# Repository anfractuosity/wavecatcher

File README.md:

# wavecatcher

https://www.anfractuosity.com/projects/wavecatcher/ - please see this website for more detail on the project.

The project will be used for acoustic cryptanalysis - "Acoustic cryptanalysis is a type of side channel attack that exploits sounds emitted by computers or other devices".

A number of aspects of computers emit ultrasound including SMPSs to inductors and capacitors present on the computer's motherboard itself.

You will likely require Kicad 5 to use the schematic/pcb layouts.

## Software

The software is now capable of extracting audio from the PDM microphone enabling playing of the audio with SoX.

I now need to swap the simple summing PDM to PCM converter, to enable better fidelity audio.

## Hardware

The PCB was manufactured and assembled using Macrofab.  I plan to eventually revise the PCB at some point
making use of line length matching of USB tracks and more curved PCB tracks.

I conducted a little benchmark of the STM32F3 chip's USB performance and get roughly 6Mbps received from it on my computer. The bandwidth
may vary a fair bit, in the order of megabits depending on your USB controller!

## Creative Commons Licence

Attribution-NonCommercial-ShareAlike 4.0 International (CC BY-NC-SA 4.0)

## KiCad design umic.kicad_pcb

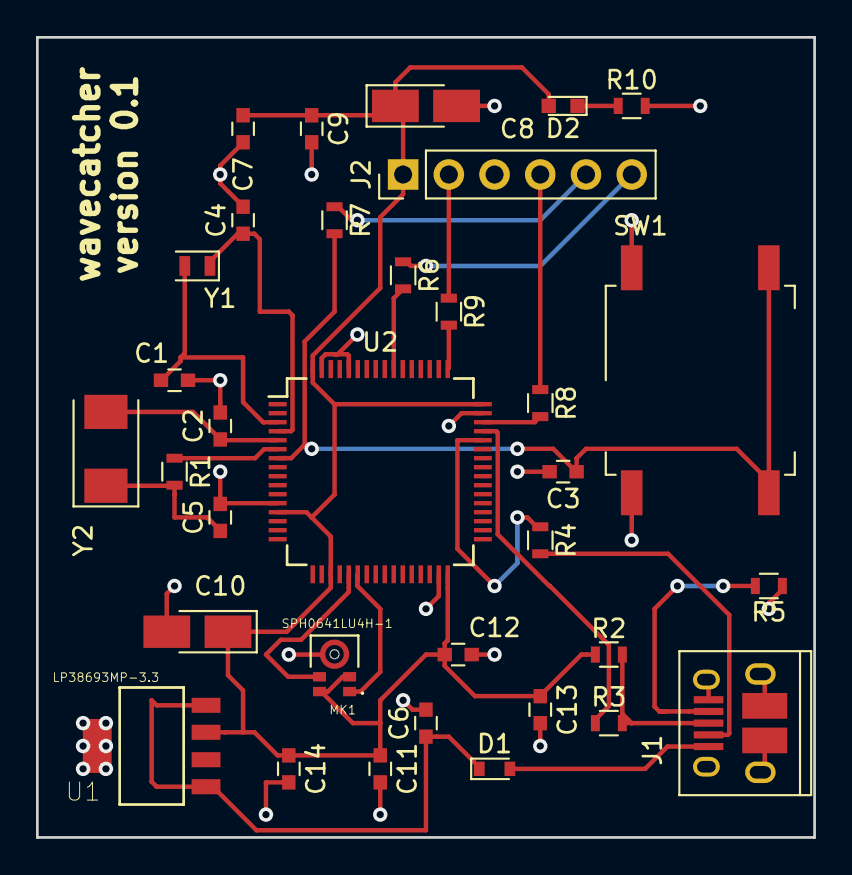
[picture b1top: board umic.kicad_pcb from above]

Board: 2 copper layers, 43.2 x 44.5 mm, 34 parts (0 on the bottom side), 25 nets.

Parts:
C1, C4: 10pF; C_0603
C2, C5: 20pF; C_0603
C3, C11, C12, C13, C14: 100nF; C_0603
C6, C7: 1uF; C_0603
C8: 1uF; CP_Tantalum_Case-R_EIA-2012-12_Hand
C9: 10nF; C_0603
C10: 4.7uF; CP_Tantalum_Case-R_EIA-2012-12_Hand
D1: D_Schottky; D_0603
D2: LED; LED_0603
J1: USB_B_Micro; USB_Micro-B_10103594-0001LF
J2: Conn_01x06; Pin_Header_Straight_1x06_Pitch2.54mm
MK1: SPH0641LU4H-1; MIC_SPH0641LU4H-1
R1: 390; R_0603
R2: 1k5; R_0603
R3, R4, R6, R7, R8, R9: 22; R_0603
R5: 100k; R_0603
R10: 68; R_0603
SW1: SW_MEC_5G; SW_MEC_5GSH9
U1: LP38693MP-3.3; SOT150P696X180-5N
U2: STM32F302RBTx; LQFP-64_10x10mm_Pitch0.5mm
Y1: 32.768kHz; Crystal_SMD_TXC_9HT11-2pin_2.0x1.2mm
Y2: 8MHz; Crystal_SMD_Abracon_ABM3-2pin_5.0x3.2mm

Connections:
+5V: D1.2, J1.1
GND: C1.2, C2.2, C3.2, C4.2, C5.2, C6.2, C7.2, C8.2, C9.2, C10.2, C11.2, C12.2, C13.2, C14.2, J1.5, J1.6, J2.3, MK1.3, R5.1, R10.2, SW1.1, SW1.2, U1.5, U2.12, U2.31, U2.47, U2.60, U2.63
unnamed: C1.1, U2.3, Y1.2
unnamed: C2.1, U2.5, Y2.2
unnamed: C3.1, R7.2, SW1.3, SW1.4, U2.7
unnamed: C4.1, U2.4, Y1.1
unnamed: C5.1, R1.2, Y2.1
unnamed: C6.1, D1.1, U1.1, U1.4
unnamed: D2.1, R10.1
unnamed: J1.2, R4.2
unnamed: J1.3, R2.2, R3.2
unnamed: J1.4, R5.2
unnamed: J2.2, R9.1
unnamed: J2.4, R8.1
unnamed: J2.5, R7.1
unnamed: J2.6, R6.1
unnamed: MK1.1, U2.22
unnamed: MK1.4, U2.21
unnamed: R1.1, U2.6
unnamed: R3.1, U2.45
unnamed: R4.1, U2.44
unnamed: R6.2, U2.55
unnamed: R8.2, U2.46
unnamed: R9.2, U2.49
VDD: C7.1, C8.1, C9.1, C10.1, C11.1, C12.1, C13.1, C14.1, D2.2, J2.1, MK1.2, MK1.5, R2.1, U1.3, U2.13, U2.19, U2.32, U2.48, U2.64

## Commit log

2018-03-25 initial
2018-03-25 power reg
2018-03-31 power
2018-04-02 commit prior to major changes
2018-04-02 working on swd
2018-04-02 removed vbat connection
2018-04-02 removed xtal resistor
2018-04-02 connected vdda up
2018-04-02 wired mems mic
2018-04-14 first draft
2018-04-14 take2: with ground plane
2018-04-14 added led
2018-04-14 sent off to fab
2018-04-16 take2 at submitting to the fab
2018-04-16 licence
2018-04-16 prototype
2018-04-16 kicad
2018-04-19 take3, connect mic to spi pins
2018-07-14 program stuff
2018-07-14 initial serial stuff
2018-07-14 readme
2018-07-14 client program
2018-07-14 makefile
2018-07-14 print data
2018-07-22 now appear to be getting some 0s and 1s from mic, need to next create a stable clock
2018-07-22 tidy
2018-07-22 use pll function instead
2018-07-22 now use 72MHz
2018-08-02 fix bug
2018-08-04 woo! we have audio
2018-08-04 PDM to PCM converter
2018-08-04 change dma transfer amount
2018-08-04 howto
2018-08-04 todo
2018-08-11 new process
2018-08-12 python filtering function
